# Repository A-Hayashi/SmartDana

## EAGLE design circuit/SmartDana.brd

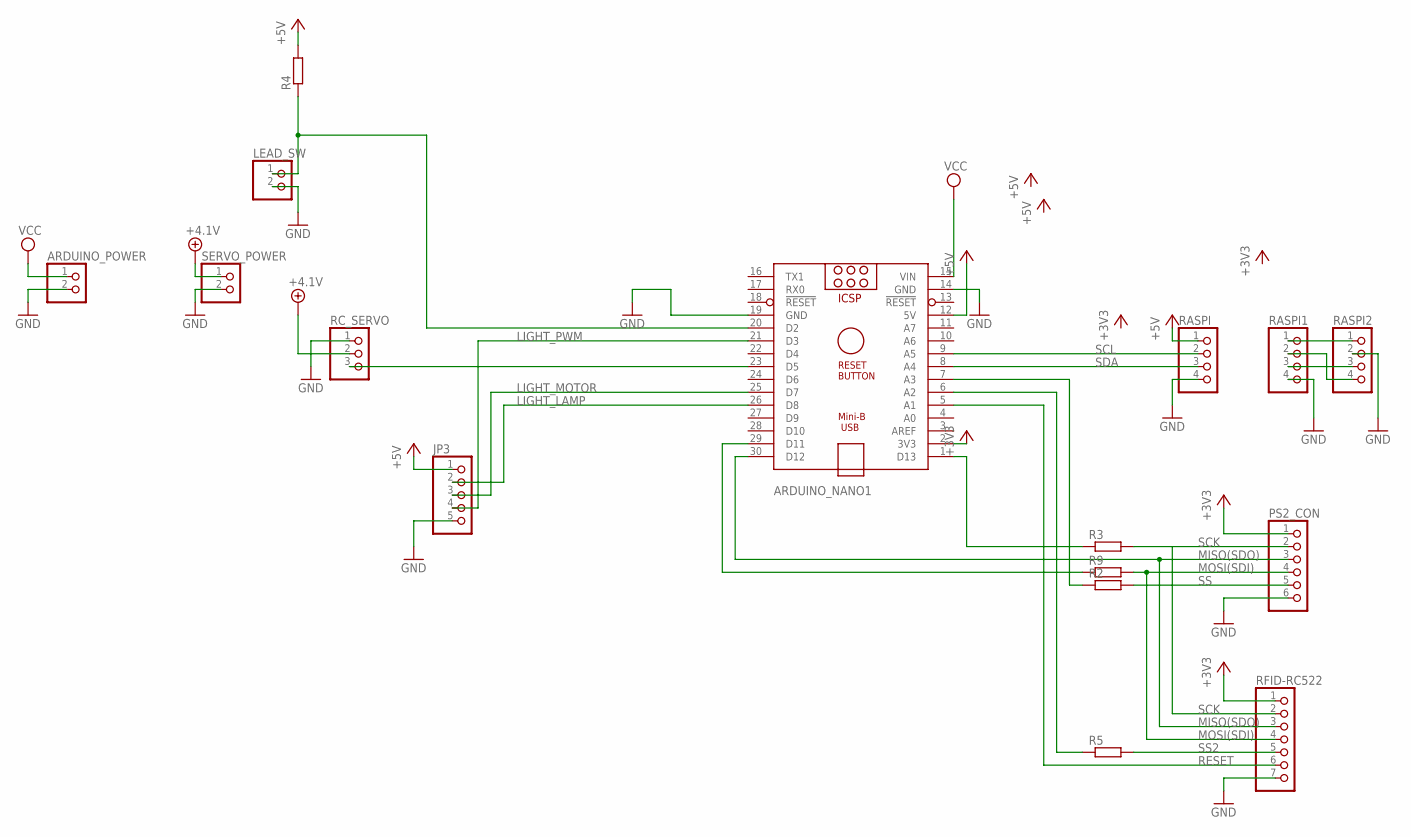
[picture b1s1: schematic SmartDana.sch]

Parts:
ARDUINO_NANO1: ARDUINO_NANO
ARDUINO_POWER: PINHD-1X2; 1X02
JP3: PINHD-1X5; 1X05
LEAD_SW: PINHD-1X2; 1X02
PS2_CON: PINHD-1X6; 1X06
R2, R3, R4, R5, R9: R-EU_0204/7; 0204/7
RASPI, RASPI1, RASPI2: PINHD-1X4; 1X04
RC_SERVO: PINHD-1X3; 1X03
RFID-RC522: PINHD-1X7; 1X07
SERVO_POWER: PINHD-1X2; 1X02

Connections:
+3V3: ARDUINO_NANO1.2 (3V3), PS2_CON.1, RFID-RC522.1
+4.1V: RC_SERVO.2, SERVO_POWER.1
+5V: ARDUINO_NANO1.12 (5V), JP3.1, R4.2, RASPI.1
GND: ARDUINO_NANO1.14 (GND), ARDUINO_NANO1.19 (GND), ARDUINO_POWER.2, JP3.5, LEAD_SW.2, PS2_CON.6, RASPI.4, RASPI1.4, RASPI2.2, RC_SERVO.1, RFID-RC522.7, SERVO_POWER.2
LIGHT_LAMP: ARDUINO_NANO1.26 (D8), JP3.2
LIGHT_MOTOR: ARDUINO_NANO1.25 (D7), JP3.3
LIGHT_PWM: ARDUINO_NANO1.21 (D3), JP3.4
MISO(SDO): ARDUINO_NANO1.30 (D12), PS2_CON.3, RFID-RC522.3
MOSI(SDI): PS2_CON.4, R9.2, RFID-RC522.4
unnamed: ARDUINO_NANO1.29 (D11), R9.1
unnamed: ARDUINO_NANO1.20 (D2), LEAD_SW.1, R4.1
unnamed: RASPI1.1, RASPI2.1
unnamed: ARDUINO_NANO1.1 (D13), R3.1
unnamed: ARDUINO_NANO1.7 (A3), R2.1
unnamed: ARDUINO_NANO1.6 (A2), R5.1
unnamed: RASPI1.2, RASPI2.4
unnamed: RASPI1.3, RASPI2.3
unnamed: ARDUINO_NANO1.23 (D5), RC_SERVO.3
RESET: ARDUINO_NANO1.5 (A1), RFID-RC522.6
SCK: PS2_CON.2, R3.2, RFID-RC522.2
SCL: ARDUINO_NANO1.9 (A5), RASPI.2
SDA: ARDUINO_NANO1.8 (A4), RASPI.3
SS: PS2_CON.5, R2.2
SS2: R5.2, RFID-RC522.5
VCC: ARDUINO_NANO1.15 (VIN), ARDUINO_POWER.1

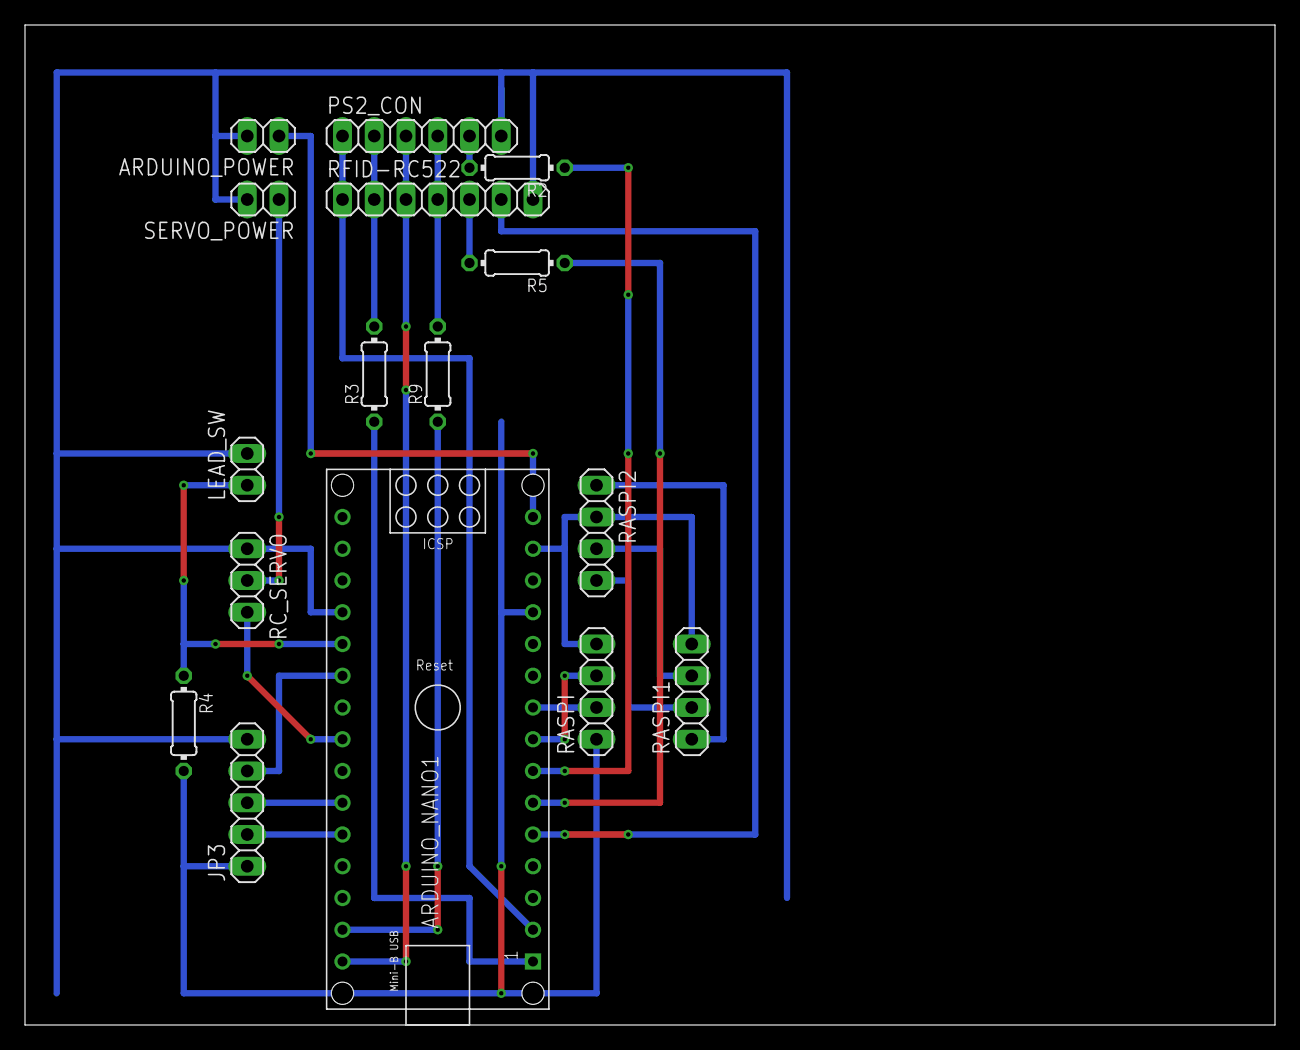
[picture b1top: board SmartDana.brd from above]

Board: 2 copper layers, 100.0 x 80.0 mm, 16 parts (0 on the bottom side), 25 nets.

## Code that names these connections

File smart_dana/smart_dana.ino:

#include "PS_PAD.h"
#include "SPI.h"
#include "MFRC522.h"
#include "VarSpeedServo.h"
#include "I2C.h"

#define A5 19
#define A4 18
#define A3 17
#define A2 16
#define A1 15
#define A0 14

#define PS2_SEL        A3
PS_PAD PAD(PS2_SEL);

#define RC522_SDA        A2
#define RC522_RESET      A1
MFRC522 rfid(RC522_SDA, RC522_RESET);

#define SERVO1_SIGNAL  5
VarSpeedServo servo1;

#define LIGHT_PWM   3
#define LIGHT_LAMP  8
#define LIGHT_MOTOR 7

#define LEAD_SW 2

bool auth_state = false;
#define AHTH_TH 10
void rfid_main()
{
  const char expected_uid[] = {0x61, 0x20, 0xC4, 0x30};
  static int auth_cnt = AHTH_TH;

  if (!rfid.PICC_IsNewCardPresent()) {
    Serial.println(F("New card is not present"));
    auth_cnt = max(auth_cnt--, 0);
    goto END;
  }

  if (!rfid.PICC_ReadCardSerial()) {
    Serial.println(F("Card cannot be read"));
    goto END;
  }

  {
    MFRC522::PICC_Type piccType = rfid.PICC_GetType(rfid.uid.sak);
    if (piccType != MFRC522::PICC_TYPE_MIFARE_MINI &&
        piccType != MFRC522::PICC_TYPE_MIFARE_1K &&
        piccType != MFRC522::PICC_TYPE_MIFARE_4K) {
      Serial.println(F("Your tag is not of type MIFARE Classic."));
      auth_cnt = max(auth_cnt--, 0);
      goto END;
    }
  }

  Serial.print("Tap card key: ");
  for (byte i = 0; i < 4; i++) {
    Serial.print(rfid.uid.uidByte[i], HEX);
    if (i < 3) {
      Serial.print(":");
    } else {
      Serial.println("");
    }
  }

  if (memcmp(expected_uid, rfid.uid.uidByte, sizeof(expected_uid)) == 0) {
    auth_cnt = AHTH_TH;
  } else {
    Serial.println("**Acces denied**");
    auth_cnt = max(auth_cnt--, 0);
  }

END:
  {

    static bool auth_state_old = false;
    auth_state = false;
    Serial.println(auth_cnt);

    if (auth_cnt > 0) {
      auth_state = true;
    } else {
      auth_state = false;
    }

    if (auth_state_old != auth_state) {
      if (auth_state == true) {
        Serial.println("false to true");
      } else {
        Serial.println("true to false");
      }
    }
    auth_state_old = auth_state;
  }
}


void setup() {
    pinMode(RC522_SDA, OUTPUT);
    digitalWrite(RC522_SDA, HIGH);
    pinMode(PS2_SEL, OUTPUT);
    digitalWrite(PS2_SEL, HIGH);

  SPI.begin();
  rfid.PCD_Init();

  pinMode(LIGHT_LAMP, OUTPUT);
  digitalWrite(LIGHT_LAMP, HIGH);
  pinMode(LIGHT_MOTOR, OUTPUT);
  digitalWrite(LIGHT_MOTOR, HIGH);
  pinMode(LIGHT_PWM, OUTPUT);
  digitalWrite(LIGHT_PWM, LOW);

  pinMode(LEAD_SW, INPUT);

  pinMode(RC522_SDA, OUTPUT);
  digitalWrite(RC522_SDA, HIGH);
  PAD.init();
  servo1.detach();
  Serial.begin(9600);
  I2C_begin(8);
}

byte pad_data[6];
byte lead_sw;
void loop() {
  static unsigned long rfid_last = 0;
  unsigned long rfid_time = 0;

//  rfid_time = millis();
//  if (rfid_time - rfid_last > 1000)
//  {
//    rfid_main();
//    rfid_last = rfid_time;
//  }
  PAD.poll();
//  interrupts();
 // if (cServo.Number == 0) {
    servo1.write(PAD.read(PS_PAD::ANALOG_RY), 30, false);
 // }

  if (!servo1.isMoving()) {
    servo1.detach();
  } else {
    servo1.attach(SERVO1_SIGNAL);
  }

  if (cPatLite.Lamp) {
    digitalWrite(LIGHT_LAMP, LOW);
  } else {
    digitalWrite(LIGHT_LAMP, HIGH);
  }

  if (PAD.read(PS_PAD::PAD_RIGHT)) {
    digitalWrite(LIGHT_MOTOR, LOW);
  } else {
    digitalWrite(LIGHT_MOTOR, HIGH);
  }
  {

    byte duty = cPatLite.Speed;
    if (duty > 0) {
      digitalWrite(LIGHT_MOTOR, LOW);
    } else {
      digitalWrite(LIGHT_MOTOR, HIGH);
    }
      pad_data[0] = PAD.read(PS_PAD::BUTTONS) & 0xff;
      pad_data[1] = (PAD.read(PS_PAD::BUTTONS) >> 8) & 0xff;
      pad_data[2] = PAD.read(PS_PAD::ANALOG_RX);
      pad_data[3] = PAD.read(PS_PAD::ANALOG_RY);
      pad_data[4] = PAD.read(PS_PAD::ANALOG_LX);
      pad_data[5] = PAD.read(PS_PAD::ANALOG_LY);
      lead_sw = (~digitalRead(LEAD_SW)) & 0x01;
    TCCR2A = 0b00100011;    //比較一致でLow、BOTTOMでHighをOC2Aﾋﾟﾝへ出力 (非反転動作)
    //高速PWM動作
    TCCR2B = 0b00001010;    //高速PWM動作, clkT2S/8 (8分周)
    // TOP値指定
    OCR2A = 99;             //16MHz/(8*(1+99))=20KHz

    OCR2B = (byte)duty;
  }
   Serial.print("PS: ");
   for(int i=0; i<6; i++){
     Serial.print(pad_data[i],HEX);
     Serial.print(":");
   }
  Serial.print(" : lead_sw");
  Serial.println(lead_sw);
   //delay(100);
  //chThdSleepMilliseconds(500);
}


void I2C_RequestCbk(byte reg, byte* p_data, byte* p_size)
{
  switch (reg) {
    // Asume that the receiving end uses the same float representation
    case Req_PsPad:
      for(int i=0; i<6; i++){
        p_data[i] = pad_data[i];
      }
      *p_size = 6;
      break;
    case Req_RC522:
      p_data[0] = auth_state;
      *p_size = 1;
      break;
    case Req_Switch:
      p_data[0] = lead_sw;
      *p_size = 1;
      break;
    default:
      break;
  }
}

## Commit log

2018-05-08 NilRTOS-Arduino導入
2018-05-08 PSコントローラ取得を割り込みで実現
2018-05-08 rfid
2018-05-10 ChRt導入
2018-05-12 RFIDとPSコントローラ同時使用可
2018-05-12 速度制御のServo使用可
2018-05-12 回転灯動作確認
2018-05-13 NodeMCU動作テスト中
2018-05-13 体重測定できた
2018-05-13 体重測定確認
2018-05-13 体重をツイート完了
2018-05-13 体重計にLED追加
2018-05-14 計測器管理(小集団活動) お試し
2018-05-16 パターン設計仮完了
2018-05-16 ラズパイからサーボとパトライト回す
2018-05-17 ラスパイとPS2コントローラ通信
2018-05-17 パトライト修正
2018-05-18 ラズパイで ・PS2コントローラ ・リードスイッチ ・パトライト ・RFID 動作確認済
2018-05-18 piのコードコミット
2018-05-20 LED array
2018-05-20 LEDマトリクス動作確認
2018-05-20 Doc追加
2018-06-24 体重をTCPで送信できた
2018-07-02 port:80に変更
2018-07-02 体重は10倍した値を送る intで扱うため
2018-07-06 LED修正
2018-07-09 小集団13班
2018-07-12 小集団動作確認完了 たまにRFID認識しない ハード要因か？
2018-07-18 RAM使用量削減
2018-08-25 ArduinoFUNクラブにて LEDを照度センサとして使用する
